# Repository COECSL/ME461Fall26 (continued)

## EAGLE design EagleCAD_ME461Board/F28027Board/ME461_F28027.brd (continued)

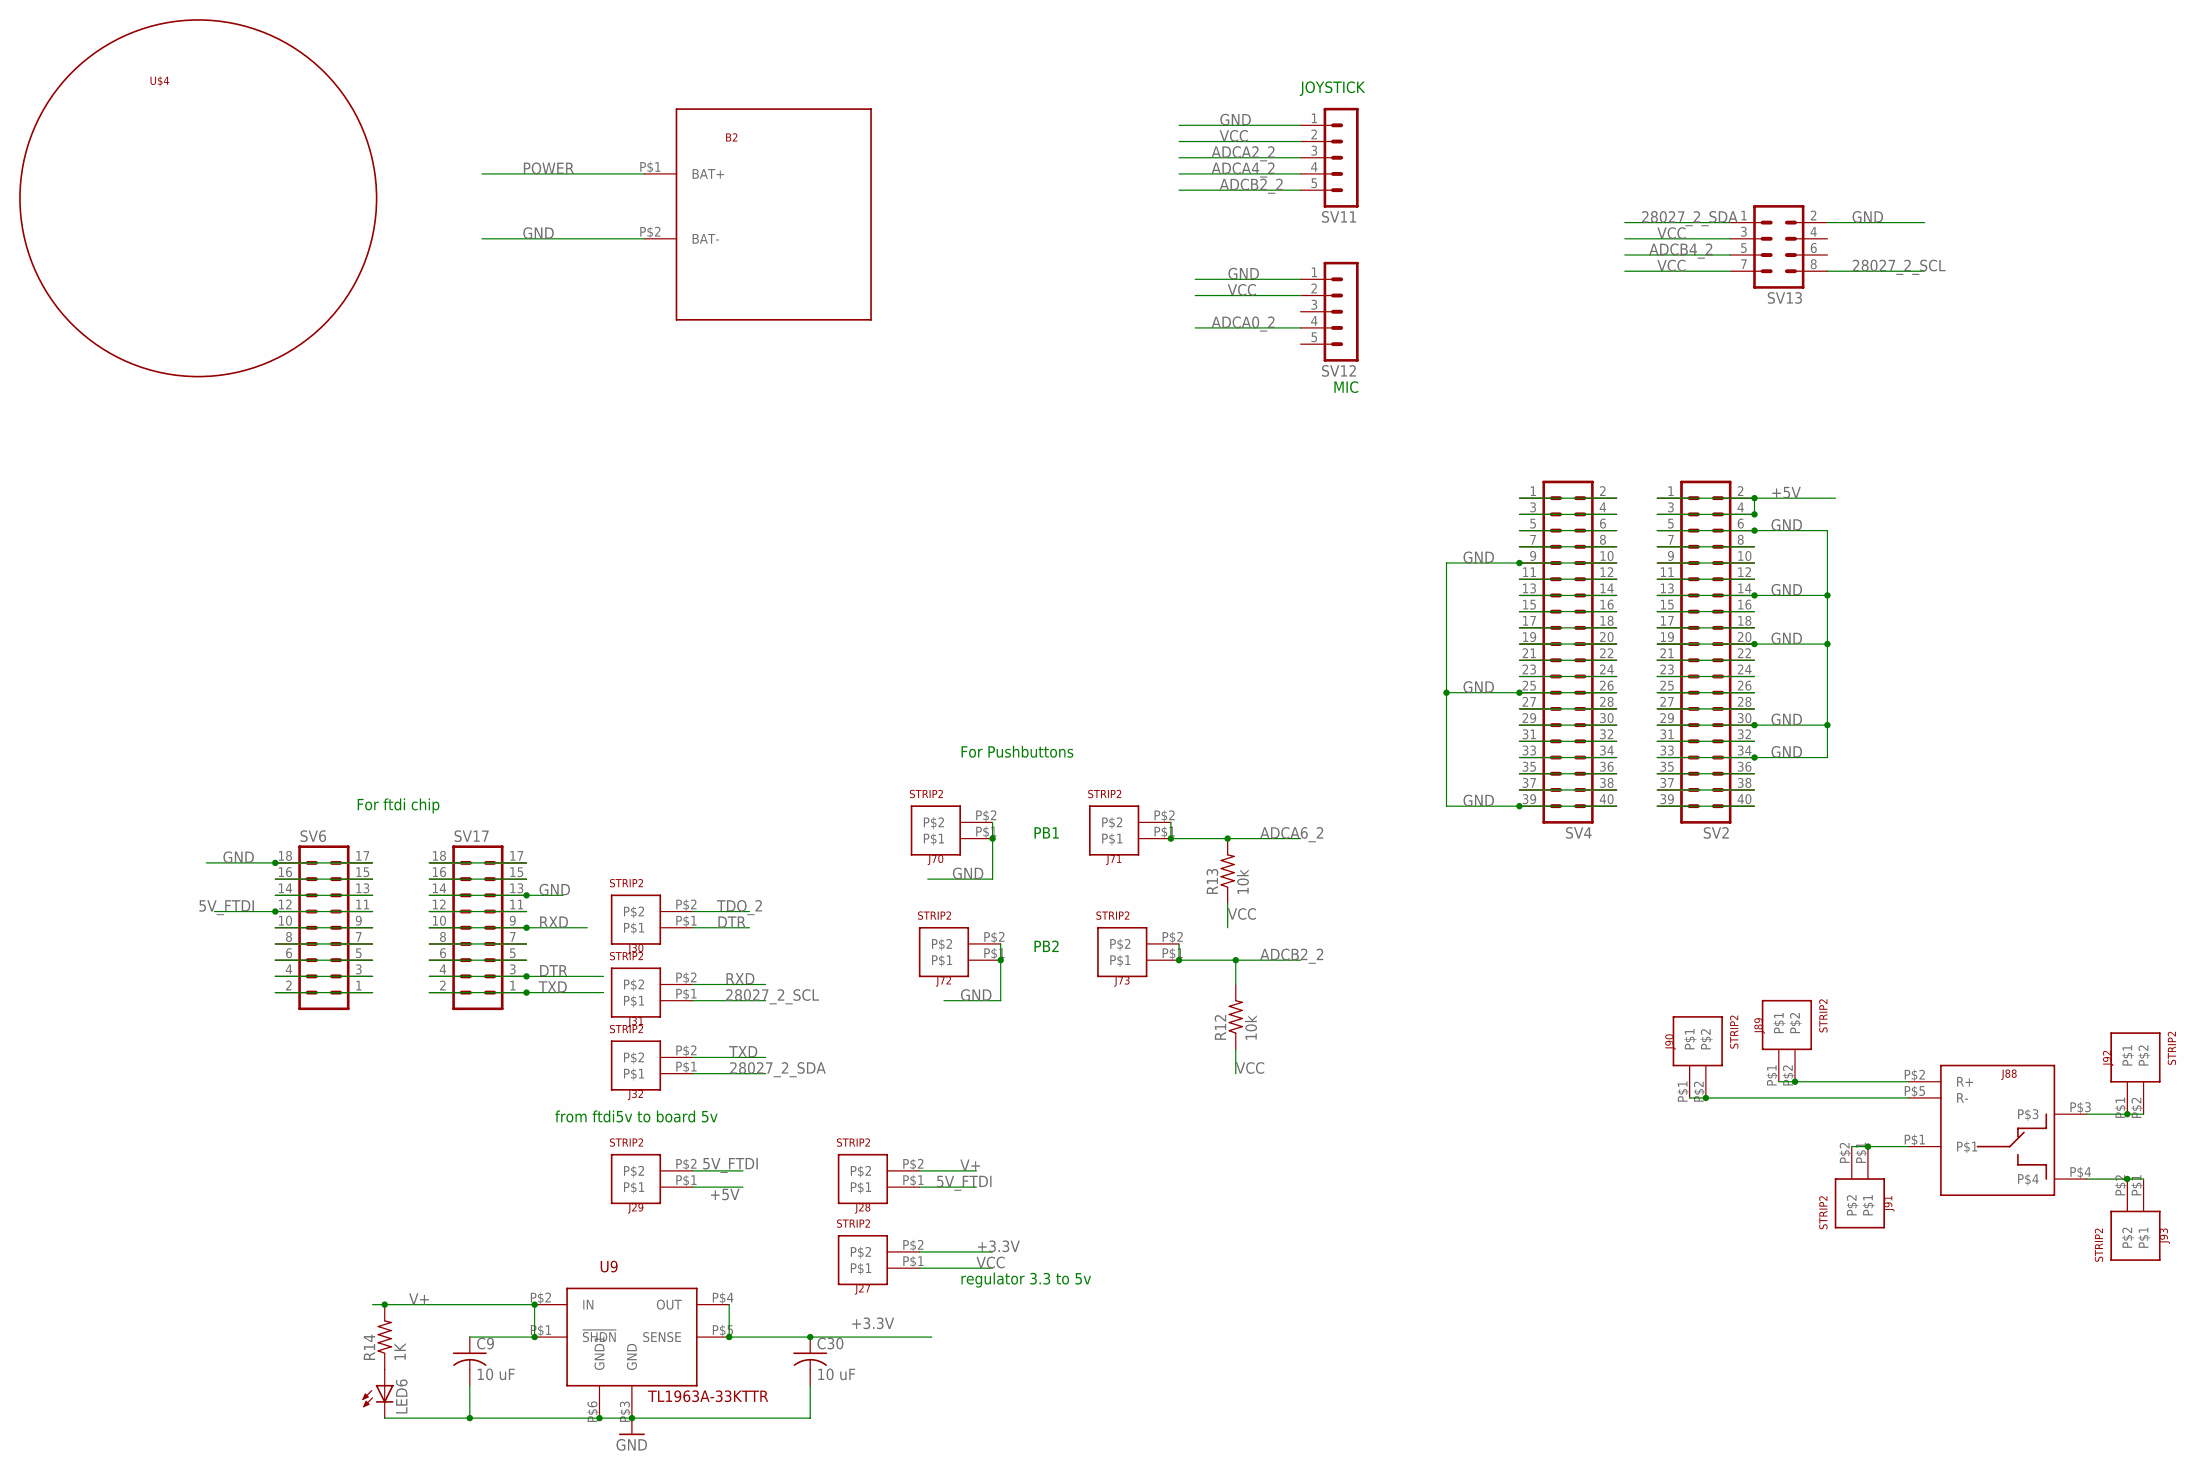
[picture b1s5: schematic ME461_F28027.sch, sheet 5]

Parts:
B2: BATTERY_4AA_HOLDER
C9, C30: 10 uF; C1206
J27, J28, J29, J30, J31, J32, J70, J71, J72, J73, J89, J90, J91, J92, J93: STRIP2
J88: RELAY_JQC-3F_5V
LED6: LEDCHIPLED_1206; CHIPLED_1206
R12, R13: 10k; R1206
R14: 1K; M1206
SV2, SV4: MA20-2
SV6, SV17: MA09-2
SV11, SV12: MA05-1
SV13: MA04-2
U9: TL1963A-33KTTR; TL1963AKTTR
U$4: CASTERWHEEL

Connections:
5V_FTDI: J28.P$1, J29.P$2, SV6.11, SV6.12
28027_2_SCL: J31.P$1, SV13.8; also elsewhere on the board
28027_2_SDA: J32.P$1, SV13.1; also elsewhere on the board
+3.3V: C30.1, J27.P$2, U9.P$4 (OUT), U9.P$5 (SENSE)
+5V: J29.P$1, SV2.1, SV2.2, SV2.3, SV2.4; also elsewhere on the board
ADCA0_2: SV12.4; also elsewhere on the board
ADCA2_2: SV11.3; also elsewhere on the board
ADCA4_2: SV11.4; also elsewhere on the board
ADCA6_2: J71.P$1, J71.P$2, R13.2; also elsewhere on the board
ADCB2_2: J73.P$1, J73.P$2, R12.2, SV11.5; also elsewhere on the board
ADCB4_2: SV13.5; also elsewhere on the board
DTR: J30.P$1, SV17.3, SV17.4
GND: B2.P$2 (BAT-), C9.2, C30.2, J70.P$1, J70.P$2, J72.P$1, J72.P$2, LED6.C, SV2.5, SV2.6, SV2.13, SV2.14, SV2.19, SV2.20, SV2.29, SV2.30, SV2.33, SV2.34, SV4.9, SV4.10, SV4.25, SV4.26, SV4.39, SV4.40, SV6.17, SV6.18, SV11.1, SV12.1, SV13.2, SV17.13, SV17.14, U9.P$3 (GND), U9.P$6 (GND1); also elsewhere on the board
unnamed: SV6.15, SV6.16
unnamed: SV6.13, SV6.14
unnamed: SV6.9, SV6.10
unnamed: SV6.7, SV6.8
unnamed: SV6.5, SV6.6
unnamed: SV6.3, SV6.4
unnamed: SV6.1, SV6.2
unnamed: SV17.5, SV17.6
unnamed: SV17.7, SV17.8
unnamed: SV17.11, SV17.12
unnamed: SV17.15, SV17.16
unnamed: SV17.17, SV17.18
unnamed: SV4.1, SV4.2
unnamed: LED6.A, R14.1
unnamed: SV4.3, SV4.4
unnamed: SV4.5, SV4.6
unnamed: SV4.7, SV4.8
unnamed: SV4.11, SV4.12
unnamed: SV4.13, SV4.14
unnamed: SV4.15, SV4.16
unnamed: SV4.17, SV4.18
unnamed: SV4.19, SV4.20
unnamed: SV4.21, SV4.22
unnamed: SV4.23, SV4.24
unnamed: SV4.27, SV4.28
unnamed: SV4.29, SV4.30
unnamed: SV4.31, SV4.32
unnamed: SV4.33, SV4.34
unnamed: SV4.35, SV4.36
unnamed: SV4.37, SV4.38
unnamed: SV2.39, SV2.40
unnamed: SV2.37, SV2.38
unnamed: SV2.35, SV2.36
unnamed: SV2.31, SV2.32
unnamed: SV2.27, SV2.28
unnamed: SV2.25, SV2.26
unnamed: SV2.23, SV2.24
unnamed: SV2.21, SV2.22
unnamed: SV2.17, SV2.18
unnamed: SV2.15, SV2.16
unnamed: SV2.11, SV2.12
unnamed: SV2.9, SV2.10
unnamed: SV2.7, SV2.8
unnamed: J88.P$2 (R+), J89.P$1, J89.P$2
unnamed: J88.P$5 (R-), J90.P$1, J90.P$2
unnamed: J88.P$1, J91.P$1, J91.P$2
unnamed: J88.P$3, J92.P$1, J92.P$2
unnamed: J88.P$4, J93.P$1, J93.P$2
POWER: B2.P$1 (BAT+); also elsewhere on the board
RXD: J31.P$2, SV17.9, SV17.10
TDO_2: J30.P$2; also elsewhere on the board
TXD: J32.P$2, SV17.1, SV17.2
V+: C9.1, J28.P$2, R14.2, U9.P$1 (!SHDN), U9.P$2 (IN)
VCC: J27.P$1, R12.1, R13.1, SV11.2, SV12.2, SV13.3, SV13.7; also elsewhere on the board

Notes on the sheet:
For Pushbuttons
For ftdi chip
JOYSTICK
MIC
PB1
PB2
from ftdi5v to board 5v
regulator 3.3 to 5v

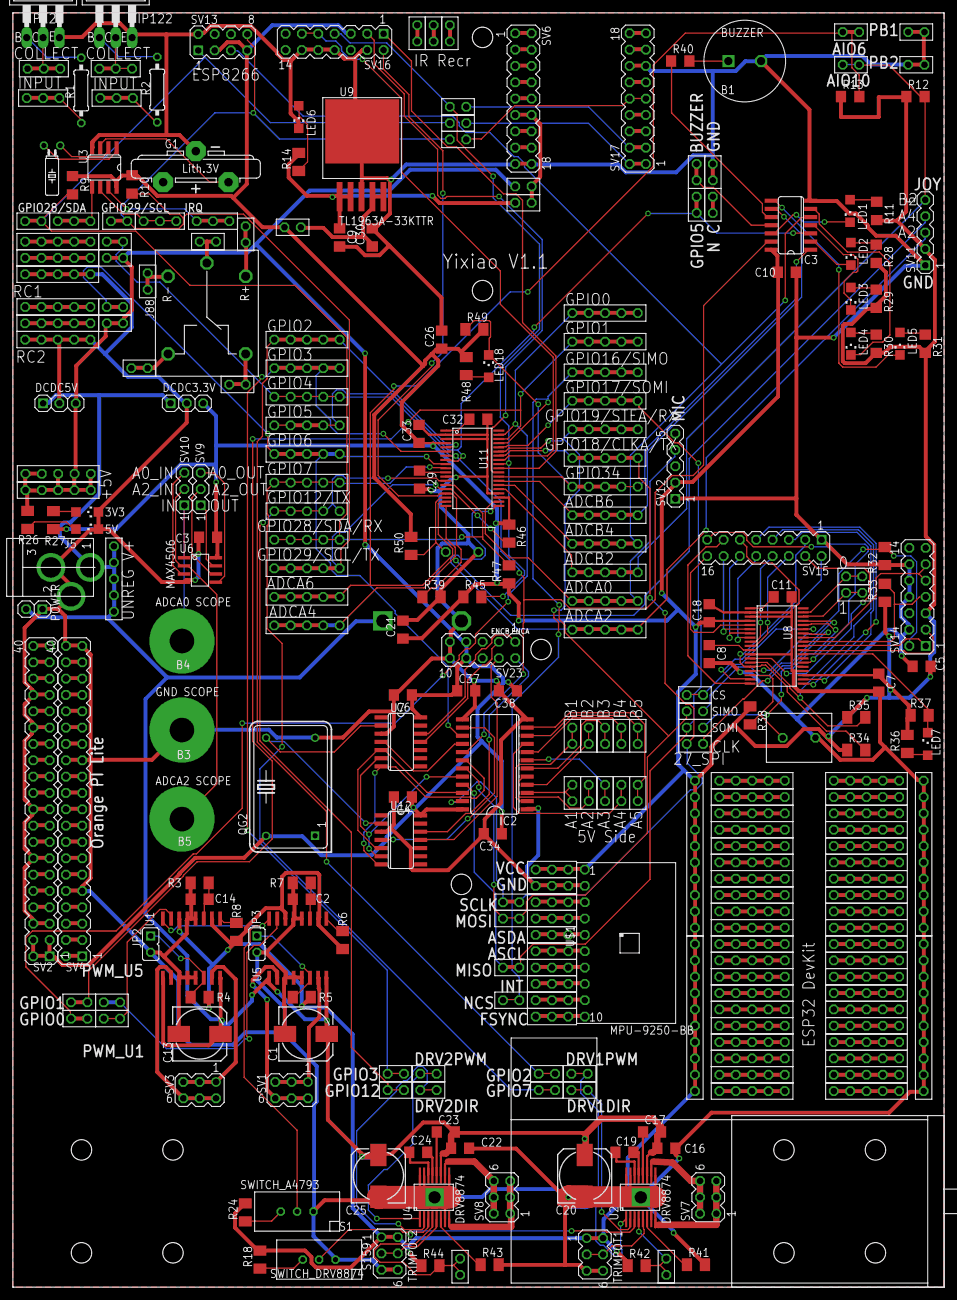
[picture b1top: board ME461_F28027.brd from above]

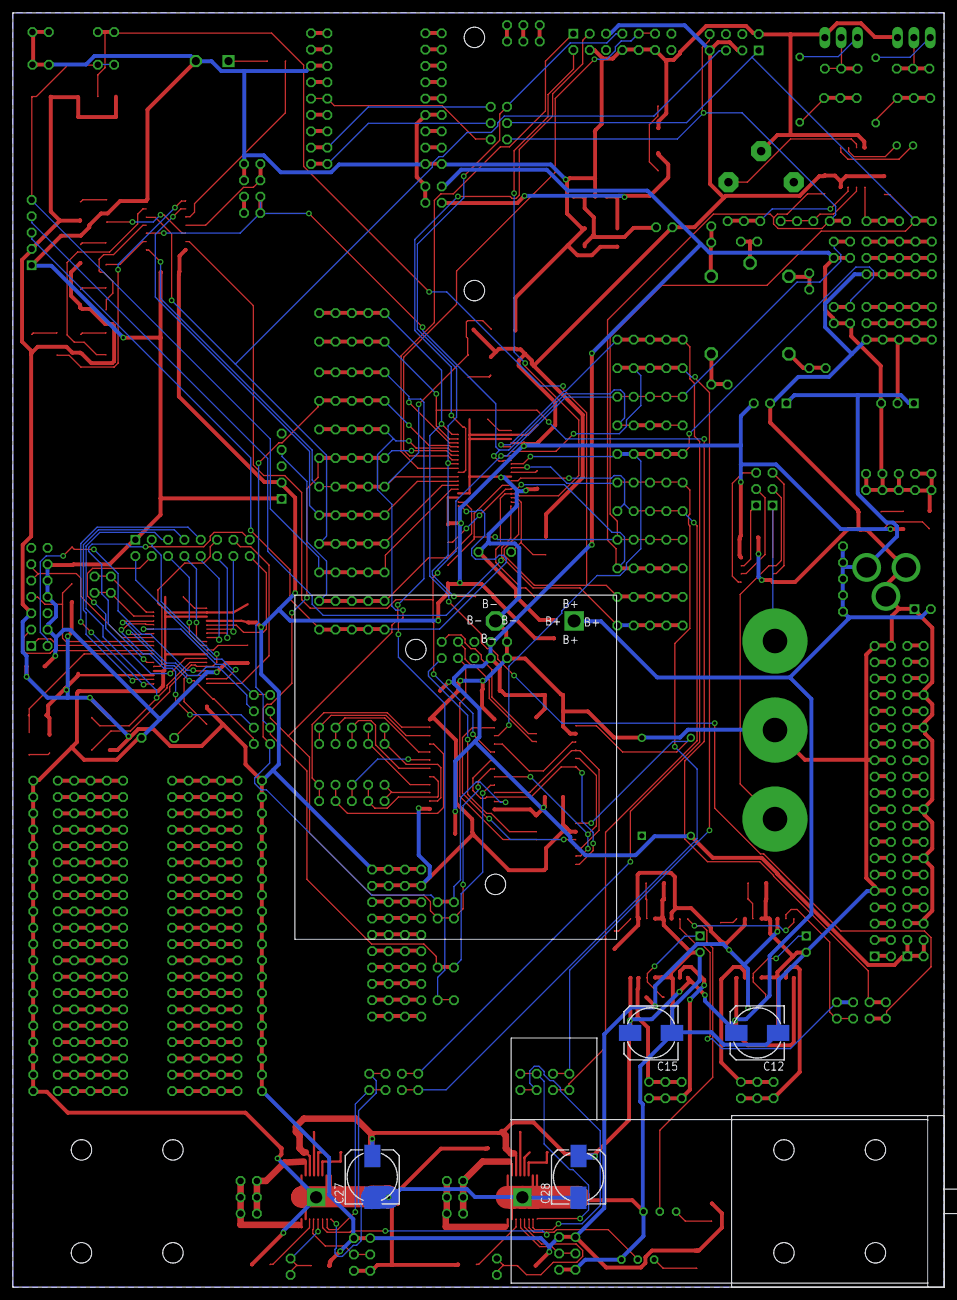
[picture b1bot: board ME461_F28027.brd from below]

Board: 2 copper layers, 144.8 x 198.1 mm, 298 parts (6 on the bottom side), 266 nets.
